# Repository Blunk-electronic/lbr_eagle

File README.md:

# eagle_libraries
Library Files for CadSoft EAGLE

supplied files: 
- CAM-Jobs (*.cam)
- Design Rules (*.dru)
- Device-Models (*.lbr)
- Scripts (*.scr)
- User Language Programs (*.ulp)
- Documentation (*.odt and *.pdf)

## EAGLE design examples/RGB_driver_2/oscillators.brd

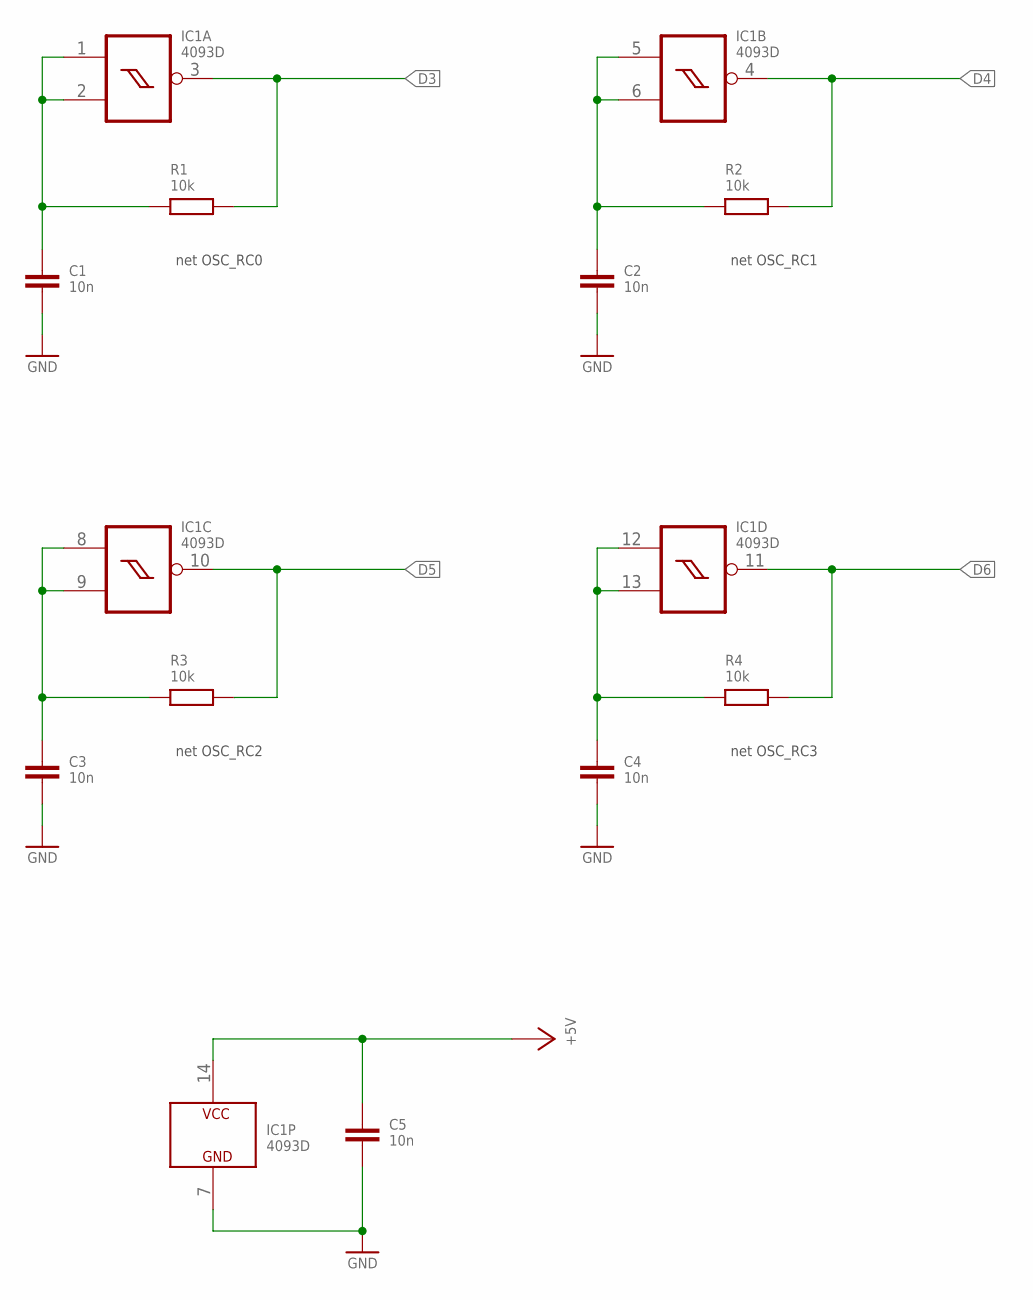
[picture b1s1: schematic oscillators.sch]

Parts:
C1, C2, C3, C4, C5: 10n; S_0805
IC1: 4093D; S_SO14
R1, R2, R3, R4: 10k; S_0805

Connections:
+5V: C5.1, IC1.14 (VCC)
D3: IC1.3 (O), R1.2
D4: IC1.4 (O), R2.2
D5: IC1.10 (O), R3.2
D6: IC1.11 (O), R4.2
GND: C1.2, C2.2, C3.2, C4.2, C5.2, IC1.7 (GND)
OSC_RC0: C1.1, IC1.1 (I0), IC1.2 (I1), R1.1
OSC_RC1: C2.1, IC1.5 (I0), IC1.6 (I1), R2.1
OSC_RC2: C3.1, IC1.8 (I0), IC1.9 (I1), R3.1
OSC_RC3: C4.1, IC1.12 (I0), IC1.13 (I1), R4.1

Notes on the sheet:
net OSC_RC0
net OSC_RC1
net OSC_RC2
net OSC_RC3

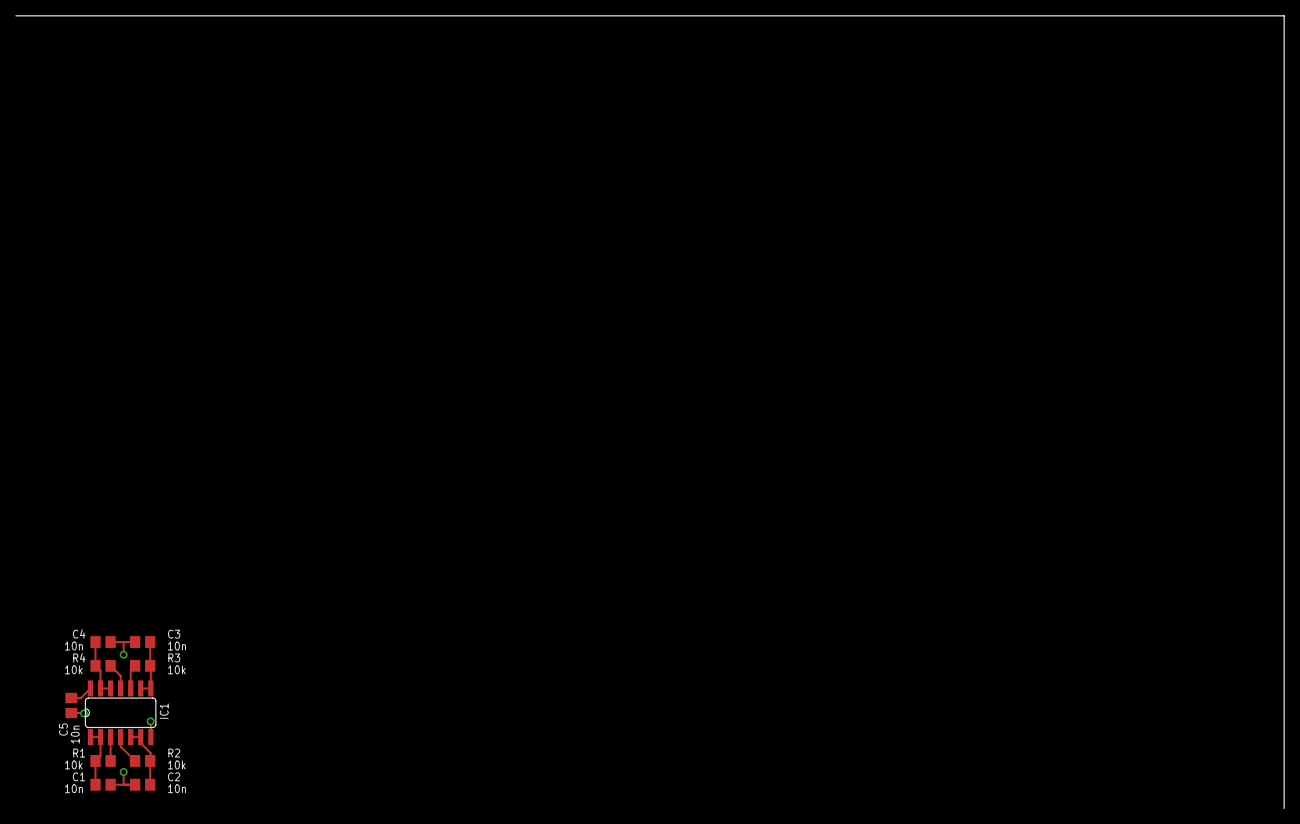
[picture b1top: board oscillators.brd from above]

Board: 2 copper layers, 10 parts (0 on the bottom side), 10 nets.

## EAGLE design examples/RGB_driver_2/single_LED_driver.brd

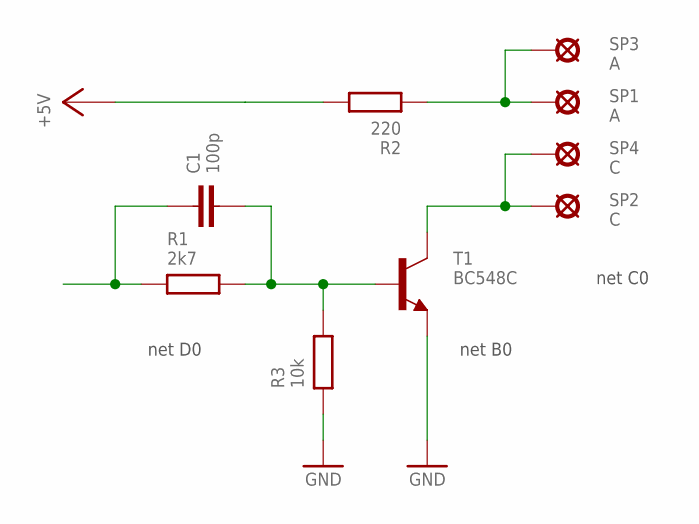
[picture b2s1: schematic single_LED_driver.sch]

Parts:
C1: 100p; S_0805
R1: 2k7; S_0805
R2: 220; S_0805
R3: 10k; S_0805
SP1, SP3: A; T_TEST_POINT_SMALL
SP2, SP4: C; T_TEST_POINT_SMALL
T1: BC548C; T_TO-92-CBE

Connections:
+5V: R2.2
A0: R2.1, SP1.1, SP3.1
B0: C1.2, R1.2, R3.2, T1.B
C0: SP2.1, SP4.1, T1.C
D0: C1.1, R1.1
GND: R3.1, T1.E

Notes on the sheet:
net D0
net B0
net C0

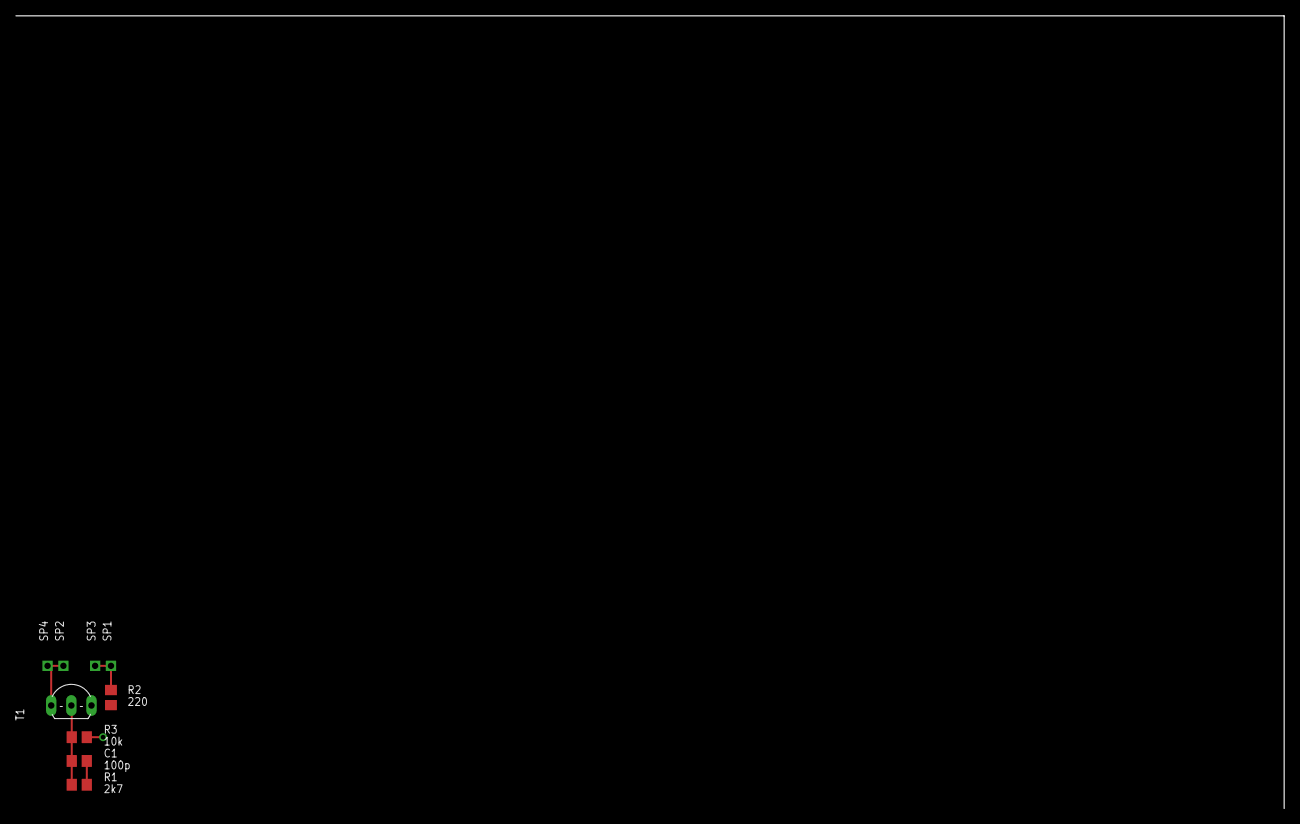
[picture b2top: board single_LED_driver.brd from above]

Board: 2 copper layers, 9 parts (0 on the bottom side), 5 nets.

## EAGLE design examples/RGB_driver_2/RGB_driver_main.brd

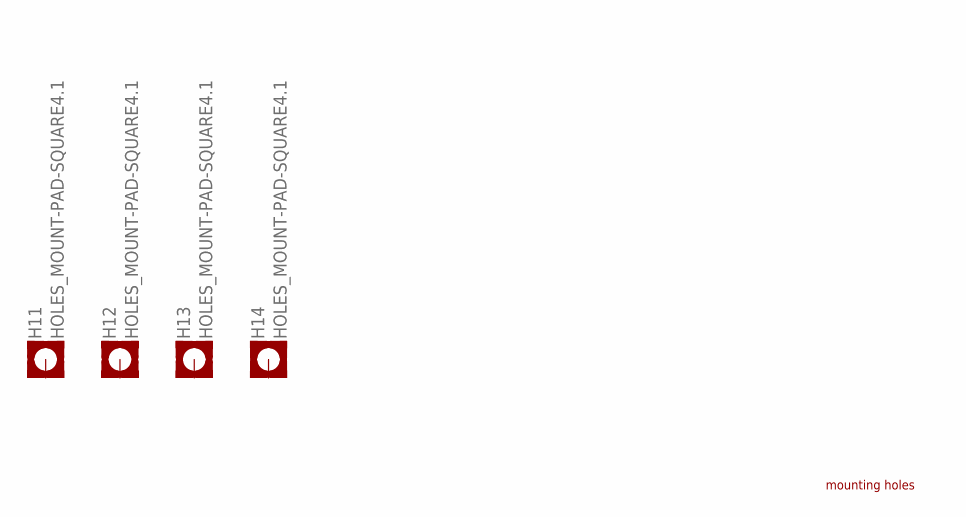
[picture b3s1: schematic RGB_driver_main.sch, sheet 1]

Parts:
H11, H12, H13, H14: HOLES_MOUNT-PAD-SQUARE4.1; HOLES_4,1-PAD-SQUARE

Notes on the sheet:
mounting holes

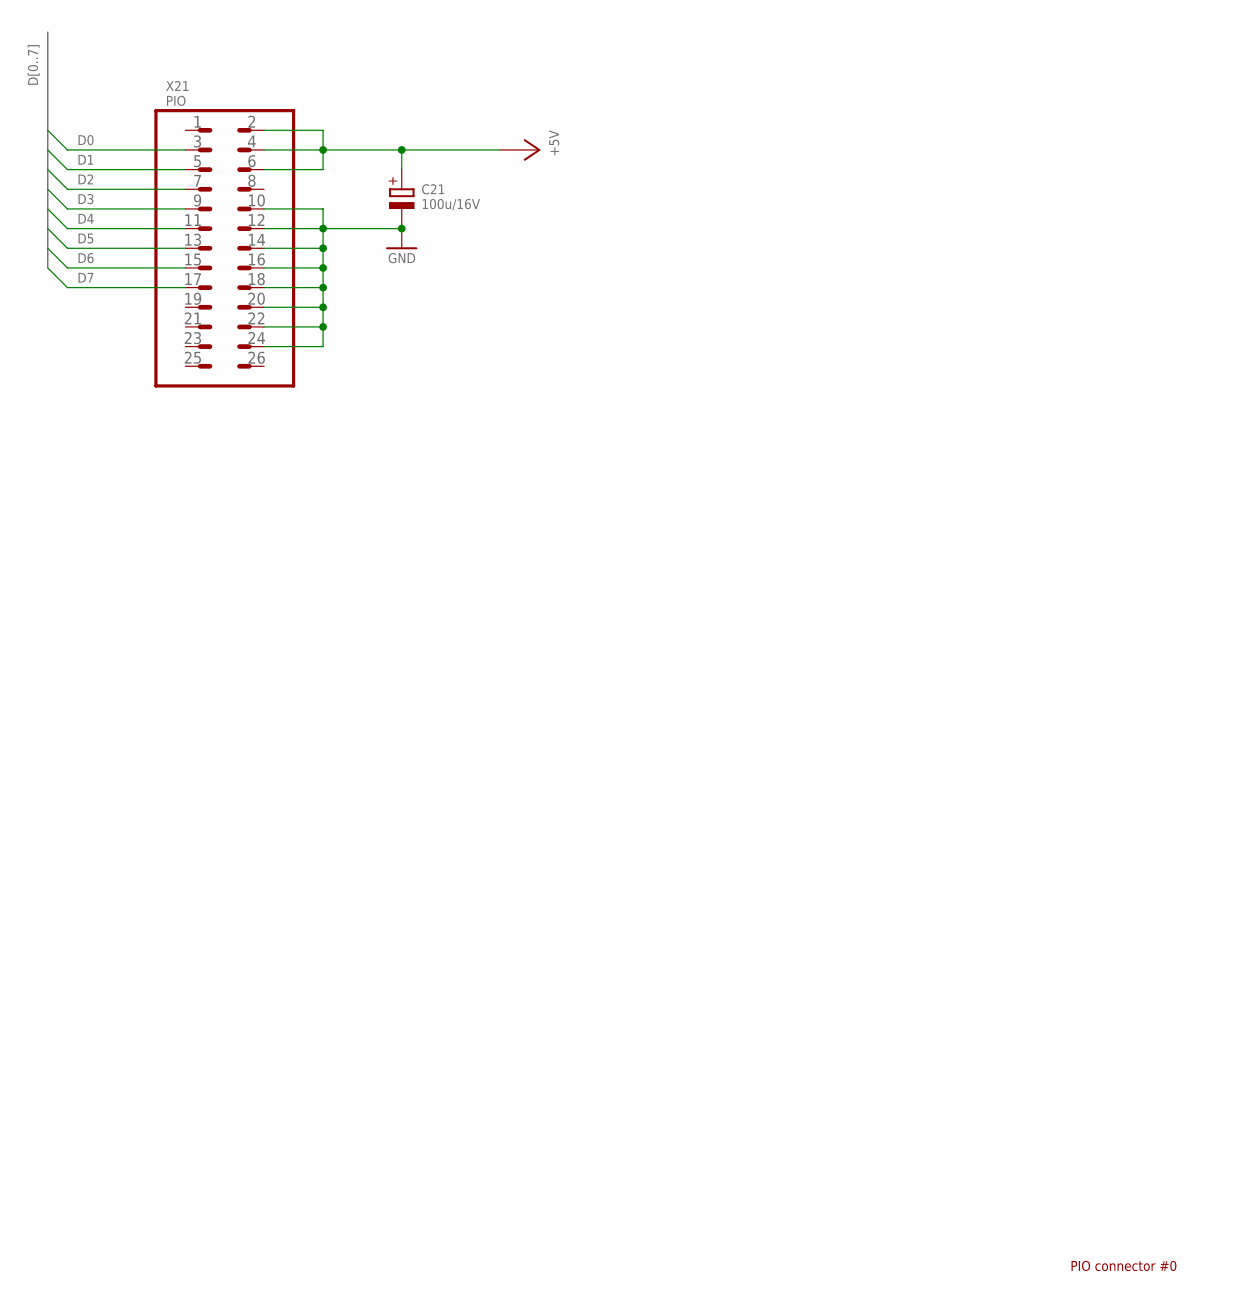
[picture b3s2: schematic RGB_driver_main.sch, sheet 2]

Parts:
C21: 100u/16V; T_D7/2.54
X21: PIO; T_PINHEAD_2X13-0

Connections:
+5V: C21.+, X21.2, X21.4, X21.6; also elsewhere on the board
D0: X21.3; also elsewhere on the board
D1: X21.5; also elsewhere on the board
D2: X21.7; also elsewhere on the board
D3: X21.9; also elsewhere on the board
D4: X21.11; also elsewhere on the board
D5: X21.13; also elsewhere on the board
D6: X21.15; also elsewhere on the board
D7: X21.17; also elsewhere on the board
GND: C21.-, X21.10, X21.12, X21.14, X21.16, X21.18, X21.20, X21.22, X21.24; also elsewhere on the board

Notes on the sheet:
PIO connector #0

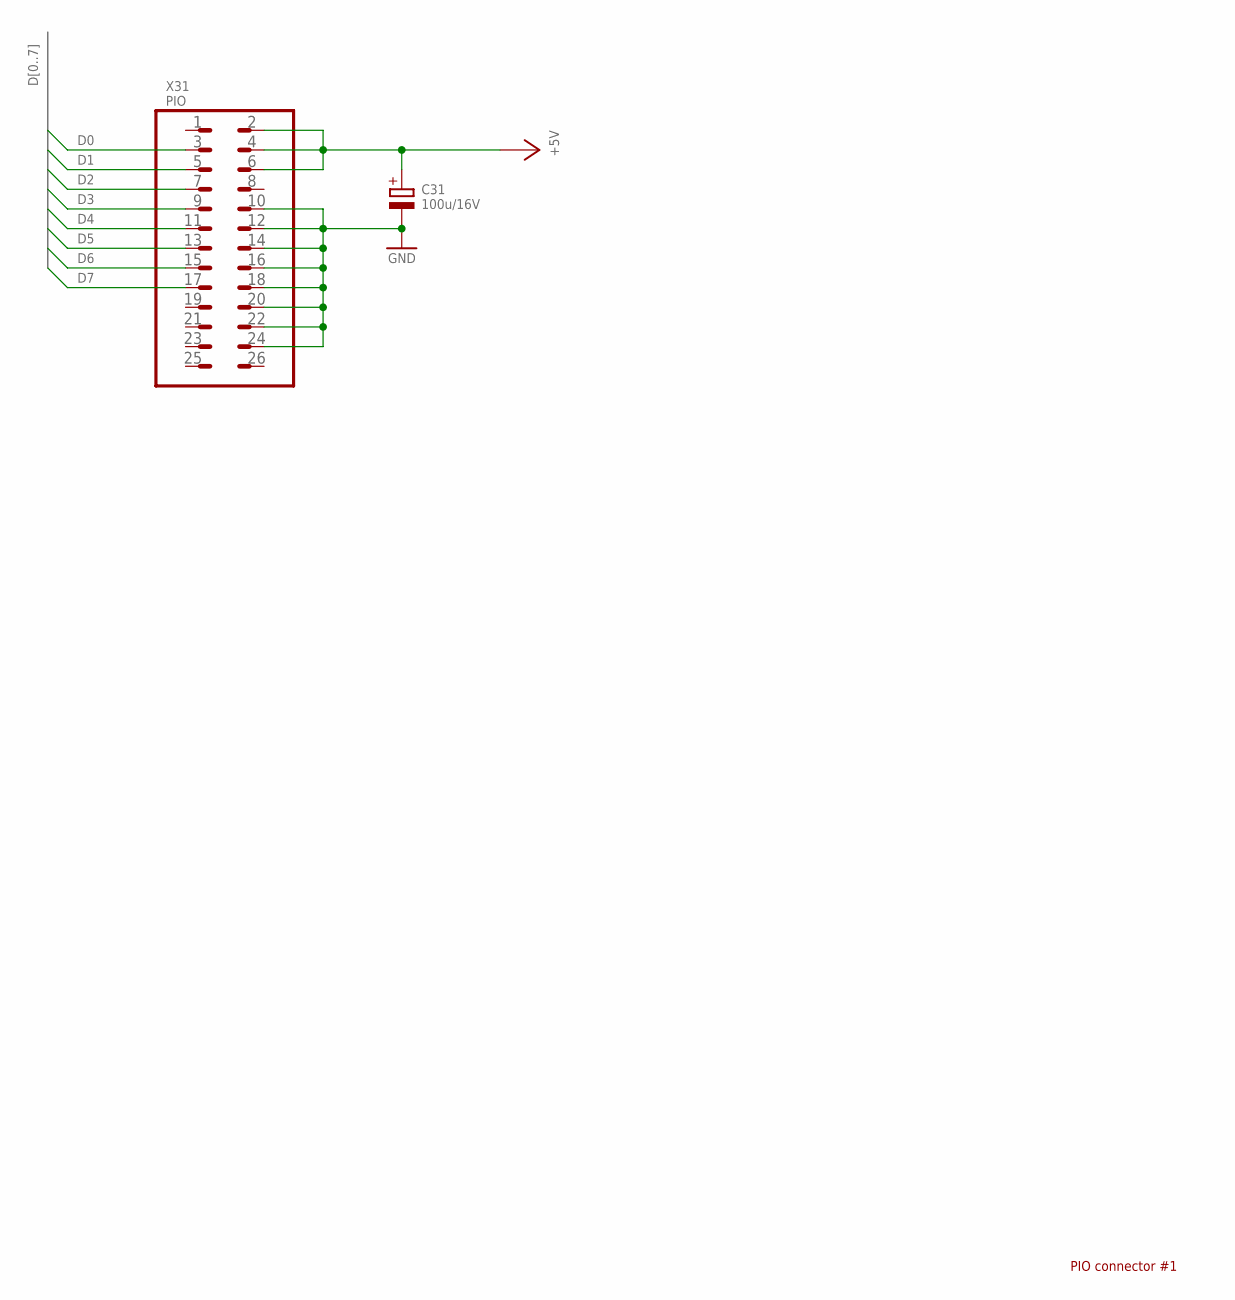
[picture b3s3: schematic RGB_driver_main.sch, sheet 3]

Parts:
C31: 100u/16V; T_D7/2.54
X31: PIO; T_PINHEAD_2X13-0

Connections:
+5V: C31.+, X31.2, X31.4, X31.6; also elsewhere on the board
D0: X31.3; also elsewhere on the board
D1: X31.5; also elsewhere on the board
D2: X31.7; also elsewhere on the board
D3: X31.9; also elsewhere on the board
D4: X31.11; also elsewhere on the board
D5: X31.13; also elsewhere on the board
D6: X31.15; also elsewhere on the board
D7: X31.17; also elsewhere on the board
GND: C31.-, X31.10, X31.12, X31.14, X31.16, X31.18, X31.20, X31.22, X31.24; also elsewhere on the board

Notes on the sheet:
PIO connector #1

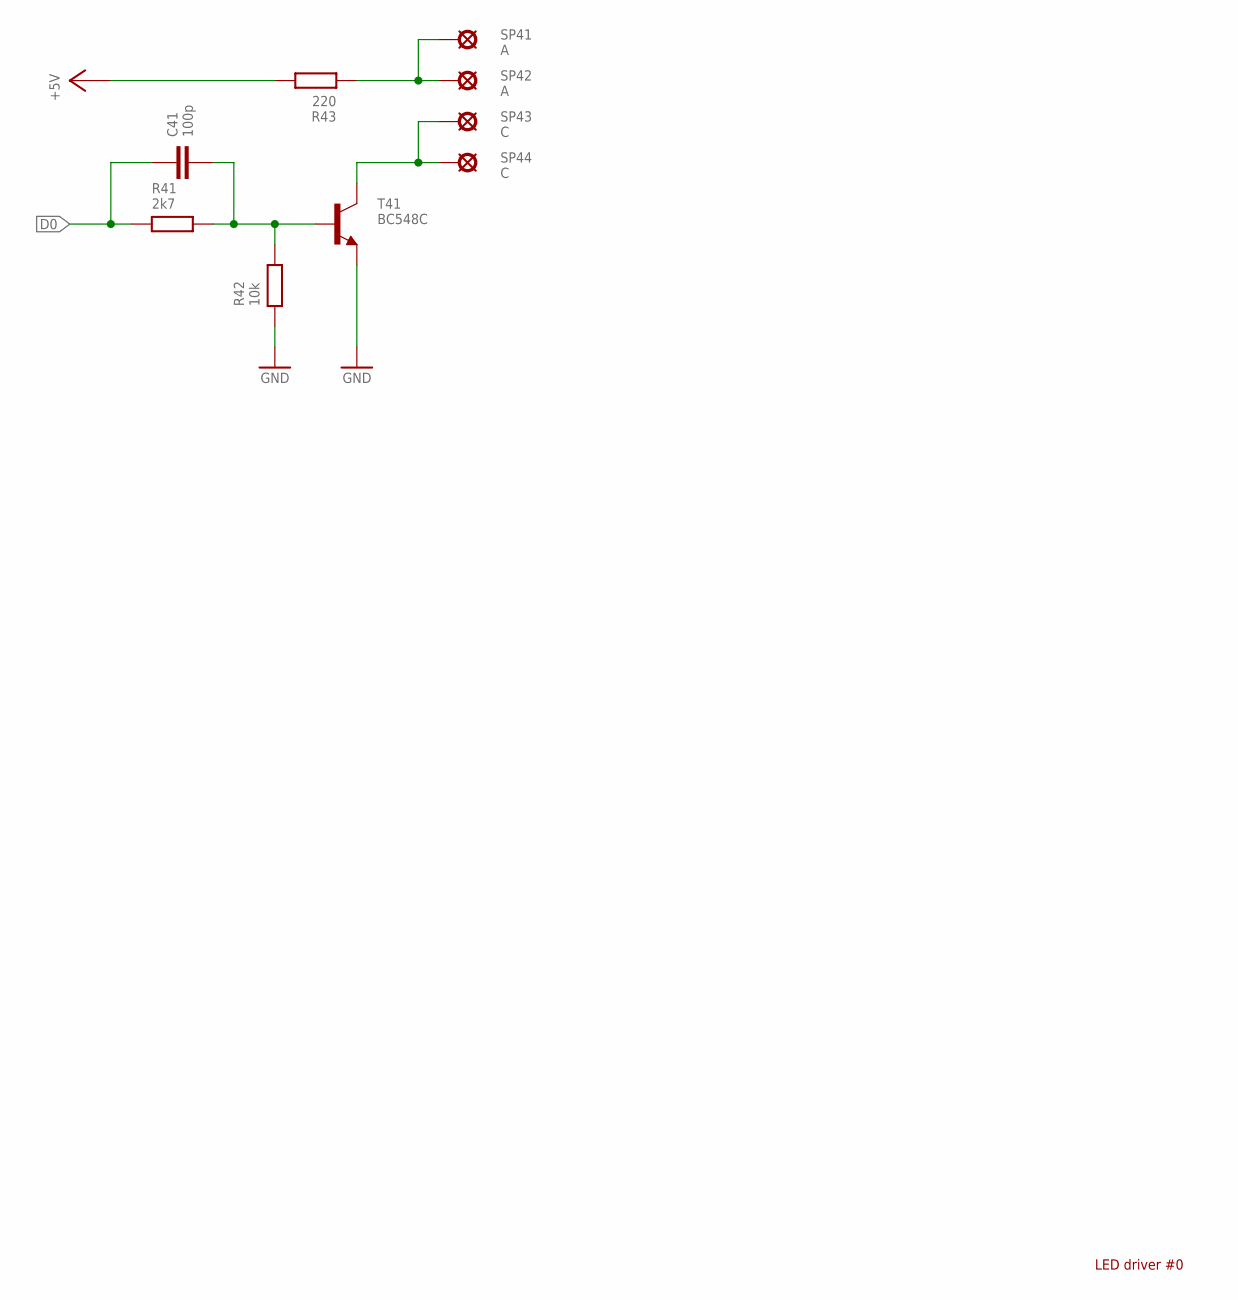
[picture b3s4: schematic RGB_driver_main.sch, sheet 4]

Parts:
C41: 100p; S_0805
R41: 2k7; S_0805
R42: 10k; S_0805
R43: 220; S_0805
SP41, SP42: A; T_TEST_POINT_SMALL
SP43, SP44: C; T_TEST_POINT_SMALL
T41: BC548C; T_TO-92-CBE

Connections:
+5V: R43.2; also elsewhere on the board
A0: R43.1, SP41.1, SP42.1
B0: C41.2, R41.2, R42.2, T41.B
C0: SP43.1, SP44.1, T41.C
D0: C41.1, R41.1; also elsewhere on the board
GND: R42.1, T41.E; also elsewhere on the board

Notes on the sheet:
LED driver #0

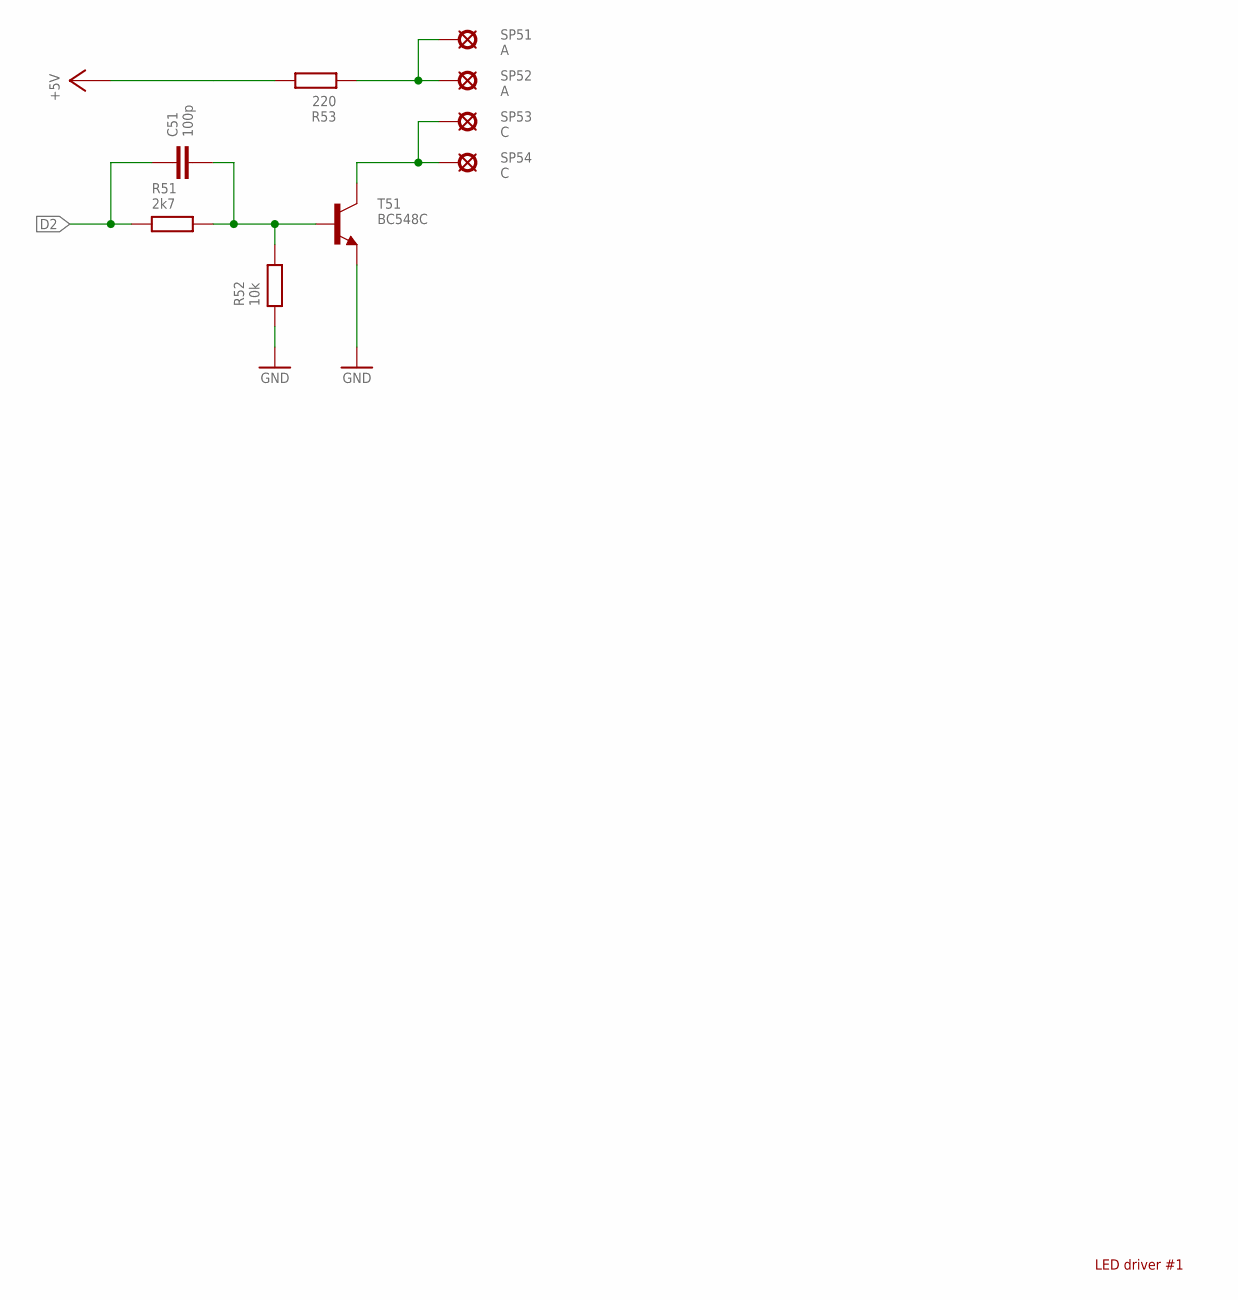
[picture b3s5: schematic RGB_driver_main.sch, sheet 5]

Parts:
C51: 100p; S_0805
R51: 2k7; S_0805
R52: 10k; S_0805
R53: 220; S_0805
SP51, SP52: A; T_TEST_POINT_SMALL
SP53, SP54: C; T_TEST_POINT_SMALL
T51: BC548C; T_TO-92-CBE

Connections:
+5V: R53.2; also elsewhere on the board
A1: R53.1, SP51.1, SP52.1
B1: C51.2, R51.2, R52.2, T51.B
C1: SP53.1, SP54.1, T51.C
D2: C51.1, R51.1; also elsewhere on the board
GND: R52.1, T51.E; also elsewhere on the board

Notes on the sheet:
LED driver #1

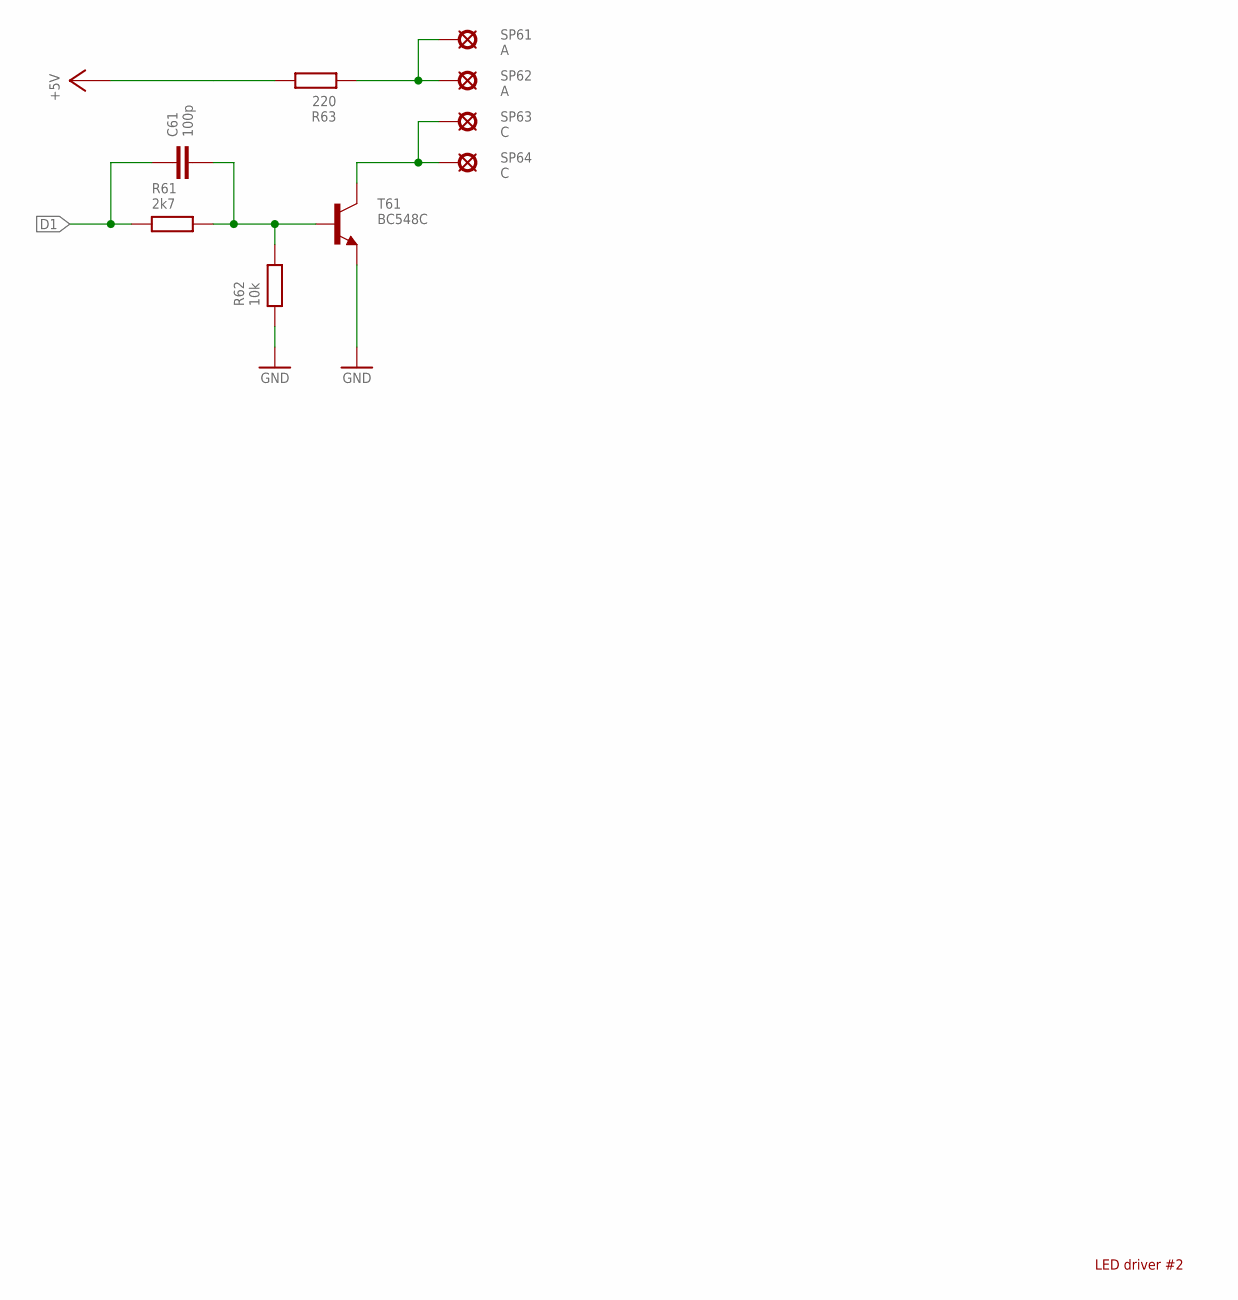
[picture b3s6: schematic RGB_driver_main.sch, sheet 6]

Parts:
C61: 100p; S_0805
R61: 2k7; S_0805
R62: 10k; S_0805
R63: 220; S_0805
SP61, SP62: A; T_TEST_POINT_SMALL
SP63, SP64: C; T_TEST_POINT_SMALL
T61: BC548C; T_TO-92-CBE

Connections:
+5V: R63.2; also elsewhere on the board
A2: R63.1, SP61.1, SP62.1
B2: C61.2, R61.2, R62.2, T61.B
C2: SP63.1, SP64.1, T61.C
D1: C61.1, R61.1; also elsewhere on the board
GND: R62.1, T61.E; also elsewhere on the board

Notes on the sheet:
LED driver #2

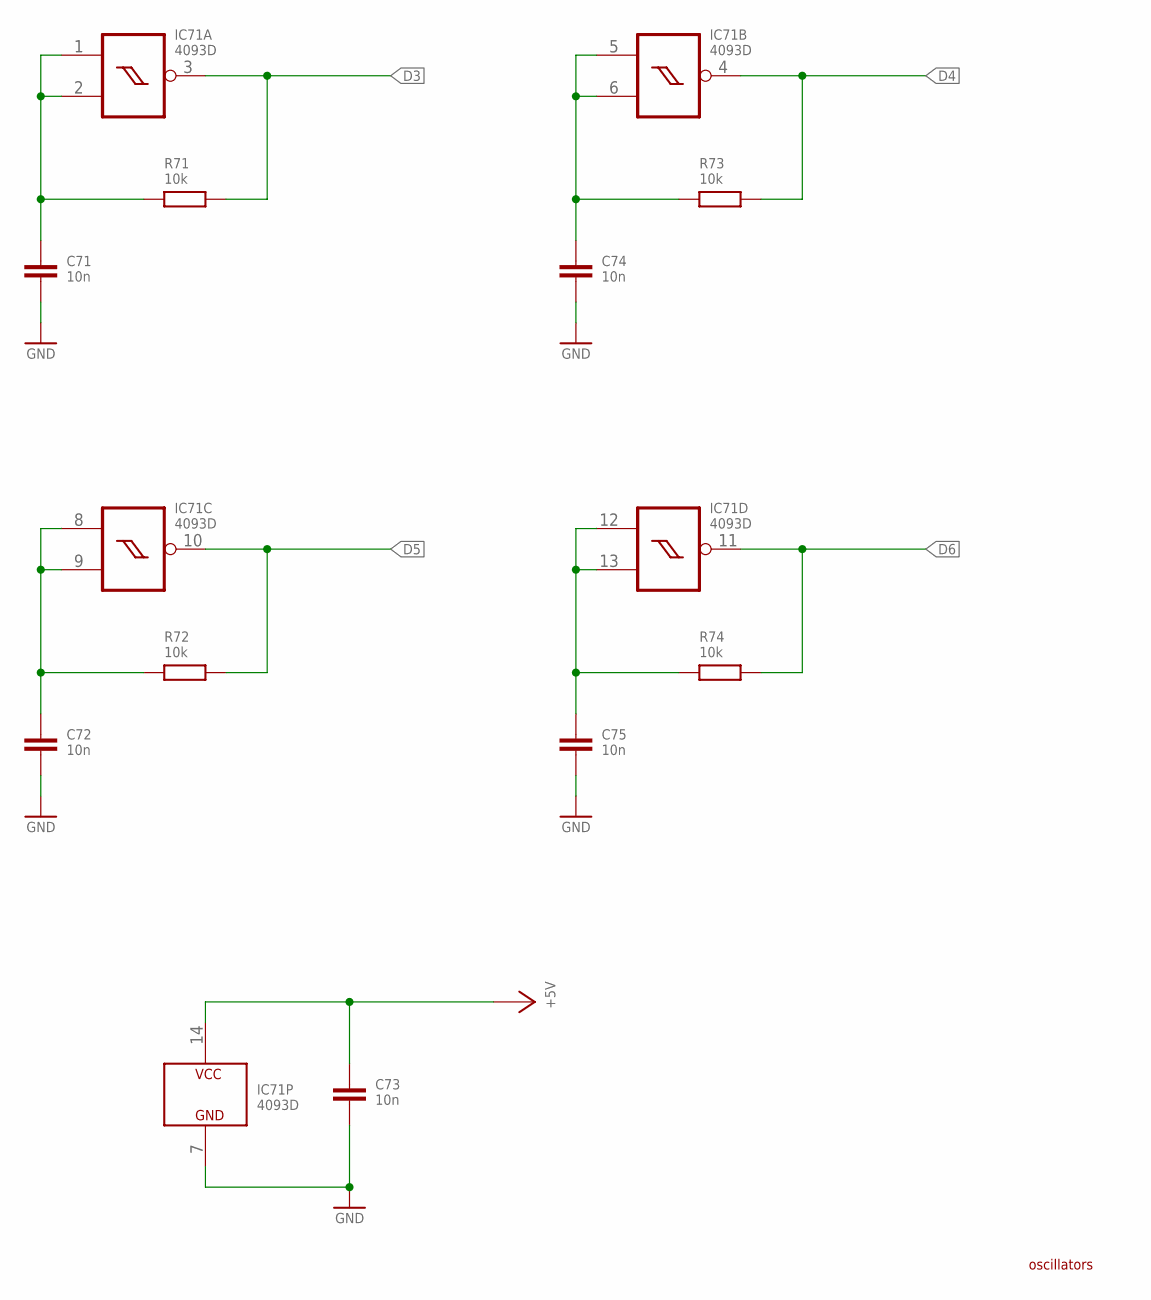
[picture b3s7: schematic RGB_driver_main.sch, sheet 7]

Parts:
C71, C72, C73, C74, C75: 10n; S_0805
IC71: 4093D; S_SO14
R71, R72, R73, R74: 10k; S_0805

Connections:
+5V: C73.1, IC71.14 (VCC); also elsewhere on the board
D3: IC71.3 (O), R71.2; also elsewhere on the board
D4: IC71.4 (O), R73.2; also elsewhere on the board
D5: IC71.10 (O), R72.2; also elsewhere on the board
D6: IC71.11 (O), R74.2; also elsewhere on the board
GND: C71.2, C72.2, C73.2, C74.2, C75.2, IC71.7 (GND); also elsewhere on the board
OSC_RC0: C71.1, IC71.1 (I0), IC71.2 (I1), R71.1
OSC_RC1: C74.1, IC71.5 (I0), IC71.6 (I1), R73.1
OSC_RC2: C72.1, IC71.8 (I0), IC71.9 (I1), R72.1
OSC_RC3: C75.1, IC71.12 (I0), IC71.13 (I1), R74.1

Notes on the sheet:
oscillators

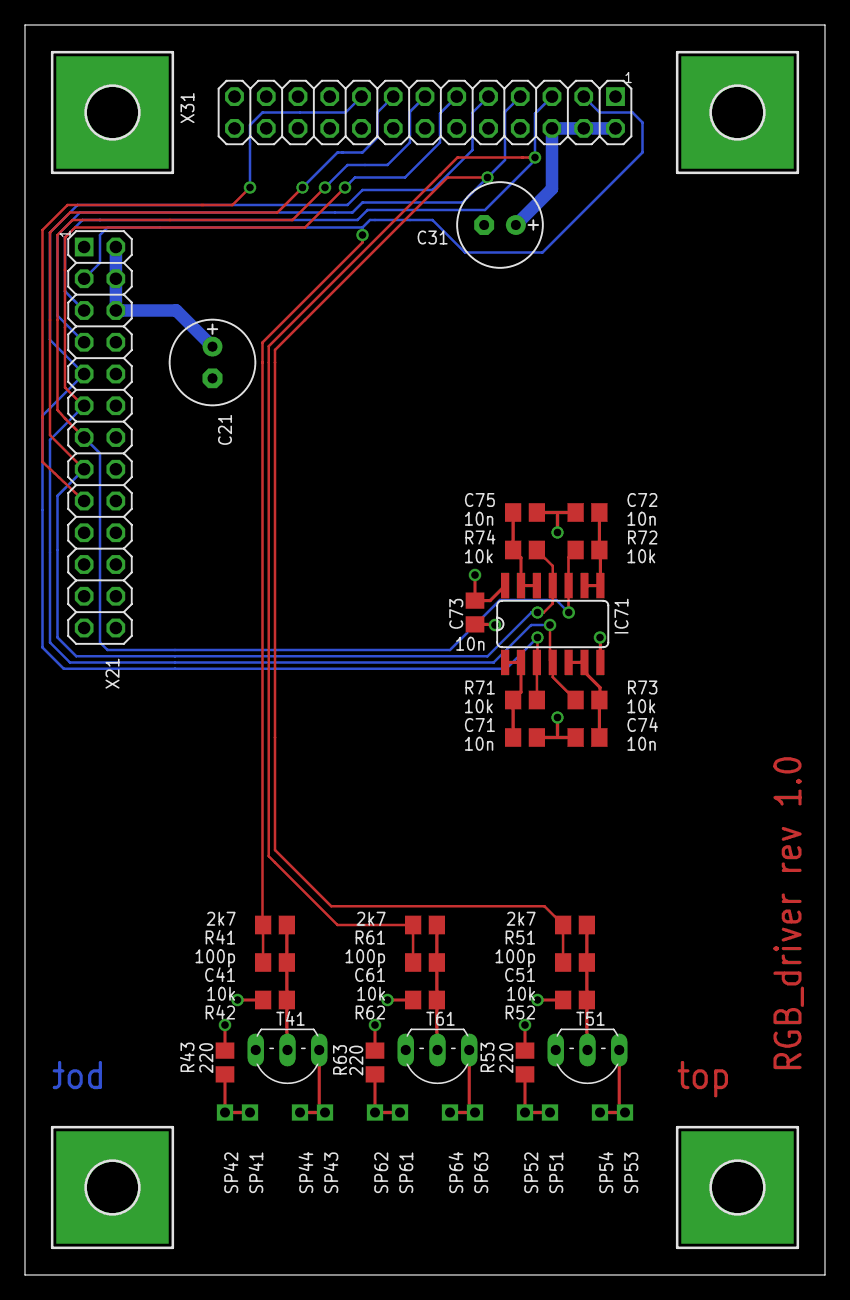
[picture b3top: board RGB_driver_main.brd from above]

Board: 4 copper layers, 64.0 x 100.0 mm, 45 parts (0 on the bottom side), 23 nets.

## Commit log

2015-10-14 updated device lbr and dru files
2015-10-14 added ignore file
2015-10-15 library update
2015-10-19 fixed attributes
2015-10-26 fixed issues with stop mask
2015-10-27 regular update
2015-11-11 updated dru
2015-11-21 bugfix
2016-07-28 added sub-dir cam
2016-11-15 added 22.5mm holder
2016-11-15 reworked relays and added current sensor
2016-11-16 added generic opamp and comparator lm311
2017-09-25 commented menu buttons
2018-05-28 renamed capacitors
2018-05-29 1206 resistor network
2018-06-21 added plcc32 package
2018-06-30 A3 frame
2018-07-31 vregs
2018-08-18 a lot of new stuff
2018-08-27 smd package for 7495
2018-09-16 74175 & 74193
2018-09-16 fixed variant names
2018-11-11 piher trimmer
2018-12-07 miniplast diodes
2018-12-09 78XX
2018-12-24 4mm capacitor
2019-01-24 disabled managed libraries
2019-02-11 fix partcodes
2019-03-28 start bcd-to-7seg decoder
2019-05-16 2x10 header in hor. variant
2019-05-16 1x4 and 1x6 horizontal header
2019-05-20 rework 2x10 header
2019-05-21 5mm LED
2019-05-22 temp sensor
2019-05-25 fix netchangers and agnd connector
2019-05-28 fix vishay resistor
2019-05-28 fix drill sizes
2019-07-10 add idf export
2019-07-11 reduced to minimal user interaction
2019-07-11 ipc exported reduced to zero user interaction
2019-07-12 reduced fabmaster exporter to minimal user interaction
2019-08-07 fix LED drills
2019-08-27 rework conf script

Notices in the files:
parts and their libraries:
be_frame: Copyright(C) 2013, Blunk electronic
